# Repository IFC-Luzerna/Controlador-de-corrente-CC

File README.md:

# Controlador de corrente CC

Projeto de um controlador de corrente CC 5A desenvolvido pelos técnicos do IFC - Campus Luzerna para ser utilizado nas disciplinas relacionadas com máquinas e acionamentos elétricos. O objetivo é utilizar esse controlador para acionar um freio acoplado diretamente a um motor de indução trifásico, criando assim um simulador de cargas. Assim, os alunos podem observar as diferentes características de acionamentos quando utilizados em diferentes situações.

Agradecimentos especiais vão para os colaboradores Clecio Jung, Darlan Klotz, Dionathan Luan de Vargas e Marcos Fiorin.

## Descritivo do projeto

Características do controlador de corrente:

- Hardware eletrônico desenvolvido no software Autodesk Eagle versão 9.6.2, e o projeto pode ser adquirido na pasta [circuito eletrônico](./circuito%20eletronico/);

- Firmware do microcontrolador ([Atmega8](https://ww1.microchip.com/downloads/en/DeviceDoc/Atmel-2486-8-bit-AVR-microcontroller-ATmega8_L_datasheet.pdf)) desenvolvido no software Microchip Studio versão 7.0, e os arquivos podem ser adquiridos na pasta [firmware](./firmware/);

- O controlador pode operar como escravo em rede Modbus RS-485:
    - O circuito de comunicação RS-485 é isolado e precisa de alimentação independente (5V ou 24V contínuos);
    - Código utilizado para implementar a comunicação provem da biblioteca [ModBus_RTU_Drivers](https://github.com/RicardoKers/ModBus_RTU_Drivers);
    - Endereço configurável através de chaves dip switch de quatro posições. O valor desejado para o endereço deve ser convertido para binário primeiro, e depois as chaves devem ser configuradas de acordo. Os endereços possíveis estão entre 0 e 15. O endereço 0 não corresponde a um endereço Modbus válido, e portanto, a comunicação Modbus é desabilitada, e o setpoint do controlador passa a ser definido pela entrada analógica 4-20mA (maiores detalhes abaixo).
    - A comunicação dispõe de três registradores de leitura e escrita (funções 3, 6 e 16 do protocolo Modbus):

| Endereço | Range      | Descrição |
| -------- | ---------- | --------- |
| 0        | 200 - 1000 | Valor amostrado da entrada analógica 4-20mA. O valor desse registrador é proporcional à corrente na entrada analógica, sendo que o valor 200 indica corrente de 4mA, e o valor 1000 indica corrente de 20mA. Caso a leitura nesse registrador indique valores inferiores a 200, a entrada está desconectada ou o cabo rompido. Escrever algum valor nesse registrador não terá efeito algum. |
| 1        | 0 - 1000   | Valor amostrado da corrente de carga. O valor desse registrador é proporcional à corrente na carga, sendo que o valor 0 indica 0A, e o valor 1000 indica 5A. Escrever algum valor nesse registrador não terá efeito algum. |
| 2        | 0 - 1000   | Referência (setpoint) de corrente. Segue o mesmo range de unidades do parâmetro anterior. Valor a ser escrito pelo mestre Modbus usado (caso esteja usando comunicação RS-485) |

- O controlador pode ainda receber a referência de corrente (setpoint) a partir da entrada analógica 4-20mA:
    - Para ativar essa opção, deve-se configurar as dip switch de configuração do endereço modbus no valor 0 (todas desabilitadas). Nesse caso, 4mA na entrada representam setpoint de 0A, e 20mA corresponde a referência de 5A. Valores inferiores a 4mA na entrada representam erro (provavelmente o cabo está rompido ou a entrada desconectada), e nesse caso o controlador desliga a carga e o led vermelho liga, indicando um erro;
    - O circuito da entrada analógica é isolado, não necesssita de alimentação independente e o sentido da corrente é arbitrario (funciona do mesmo jeito se a corrente na entrada analógica for positiva ou negativa);

- Quando o led vermelho na placa de circuito eletrônico estiver ligado, um erro ocorreu. Até o momento, apenas um erro é reportado:
    - Quando o setpoint é informado pela entrada analogica e o valor amostrado nessa entrada é inferior a 4mA (provavelmente o cabo está rompido ou a entrada desconectada);

- Na pasta [scada](./scada/) temos uma aplicação desktop simplista desenvolvida no software Elipse E3 (necessário instalá-lo para rodar a aplicação), onde a comunicação com o controlador já está implementada;

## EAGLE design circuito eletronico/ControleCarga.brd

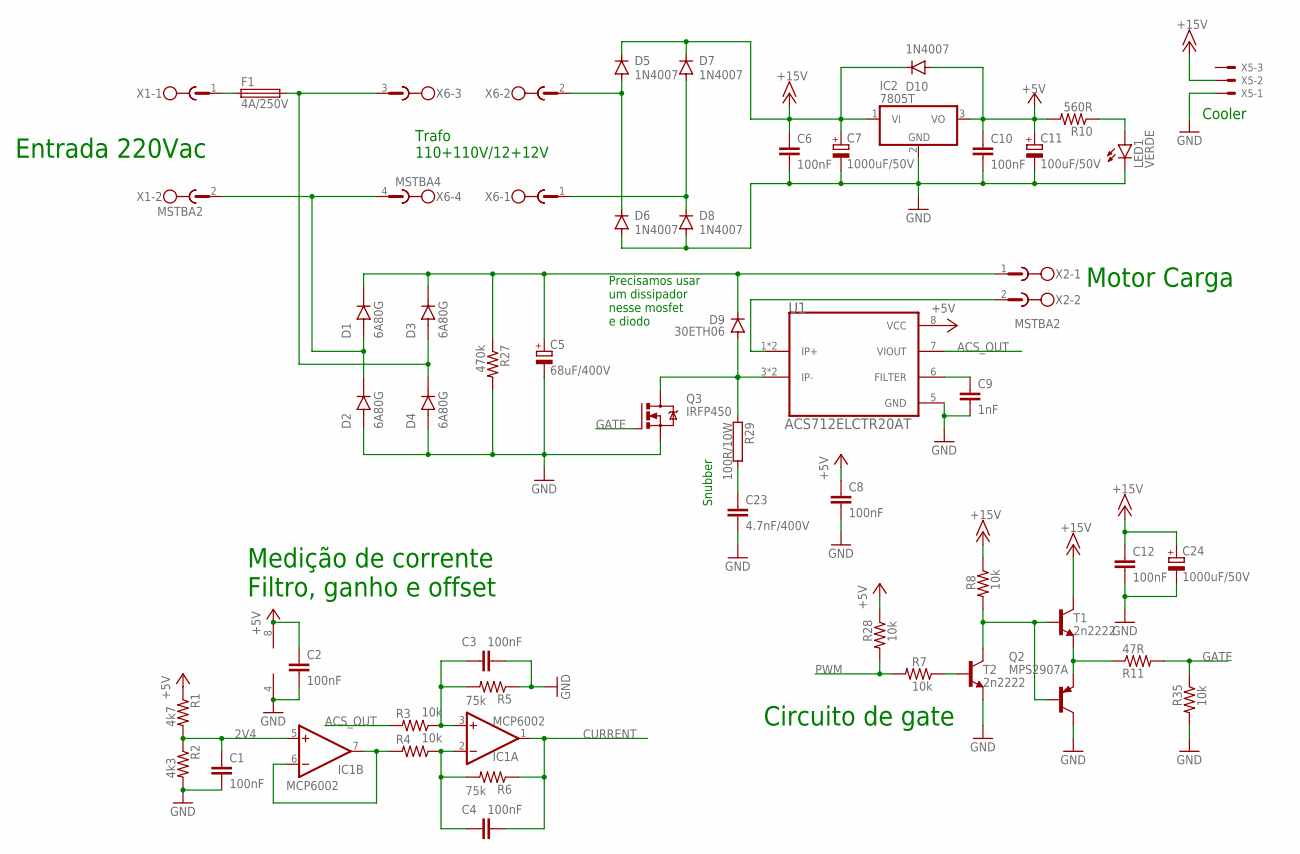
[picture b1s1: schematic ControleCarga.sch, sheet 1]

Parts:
C1, C2, C3, C4, C6, C8, C10, C12: 100nF; C050-025X075
C5: 68uF/400V; E7,5-18
C7, C24: 1000uF/50V; E5-13
C9: 1nF; C025-024X044
C11: 100uF/50V; E3,5-8
C23: 4.7nF/400V; C102-043X133
D1, D2, D3, D4: 6A80G; DIOAD1950W125L885D700
D5, D6, D7, D8, D10: 1N4007; DO41-10
D9: 30ETH06; TO220ACS
F1: 4A/250V; SH22
IC1: MCP6002; SO08
IC2: 7805T; TO220H
LED1: VERDE; LED5MM
Q2: MPS2907A; TO92-CBE
Q3: IRFP450; TO247BV
R1: 4k7; 0207/10
R2: 4k3; 0207/10
R3, R4, R7, R8, R28, R35: 10k; 0207/10
R5, R6: 75k; 0207/10
R10: 560R; 0207/10
R11: 47R; 0207/10
R27: 470k; 0207/10
R29: 100R/10W; KH216-8
T1, T2: 2n2222; TO92-EBC
U1: ACS712ELCTR20AT; SOIC127P600X175-8N
X1, X2: MSTBA2
X5: KK-156-3
X6: MSTBA4

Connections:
2V4: C1.1, IC1.5 (+IN), R1.2, R2.1
+5V: C2.1, C8.1, C10.1, C11.+, D10.A, IC1.8 (V+), IC2.3 (VO), R1.1, R10.2, R28.1, U1.8 (VCC); also elsewhere on the board
+15V: C6.1, C7.+, C12.1, C24.+, D5.C, D7.C, D10.C, IC2.1 (VI), R8.1, T1.C, X5.2
ACS_OUT: R3.2, U1.7 (VIOUT)
CURRENT: C4.2, IC1.1 (OUT), R6.1; also elsewhere on the board
GATE: Q3.G, R11.2, R35.1
GND: C1.2, C2.2, C3.2, C5.-, C6.2, C7.-, C8.2, C9.2, C10.2, C11.-, C12.2, C23.2, C24.-, D2.A, D4.A, D6.A, D8.A, IC1.4 (V-), IC2.2 (GND), LED1.K (C), Q2.C, Q3.S, R2.2, R5.1, R27.2, R35.2, T2.E, U1.5 (GND), X5.1; also elsewhere on the board
unnamed: D7.A, D8.C, X6.1
unnamed: C23.1, R29.2
unnamed: Q2.E, R11.1, T1.E
unnamed: LED1.A, R10.1
unnamed: D3.A, D4.C (K), F1.2, X6.3
unnamed: D1.A, D2.C (K), X1.2, X6.4
unnamed: U1.1 (IP+), U1.2 (IP+), X2.2
unnamed: D9.A, Q3.D, R29.1, U1.3 (IP-), U1.4 (IP-)
unnamed: C5.+, D1.C (K), D3.C (K), D9.C, R27.1, X2.1
unnamed: C9.1, U1.6 (FILTER)
unnamed: IC1.6 (-IN), IC1.7 (OUT), R4.2
unnamed: C4.1, IC1.2 (-IN), R4.1, R6.2
unnamed: C3.1, IC1.3 (+IN), R3.1, R5.2
unnamed: F1.1, X1.1
unnamed: R7.1, T2.B
unnamed: D5.A, D6.C, X6.2
unnamed: Q2.B, R8.2, T1.B, T2.C
PWM: R7.2, R28.2; also elsewhere on the board

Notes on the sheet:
Entrada 220Vac
Medição de corrente Filtro, ganho e offset
Motor Carga
Circuito de gate
Precisamos usar um dissipador nesse mosfet e diodo
Trafo 110+110V/12+12V
Snubber
Cooler

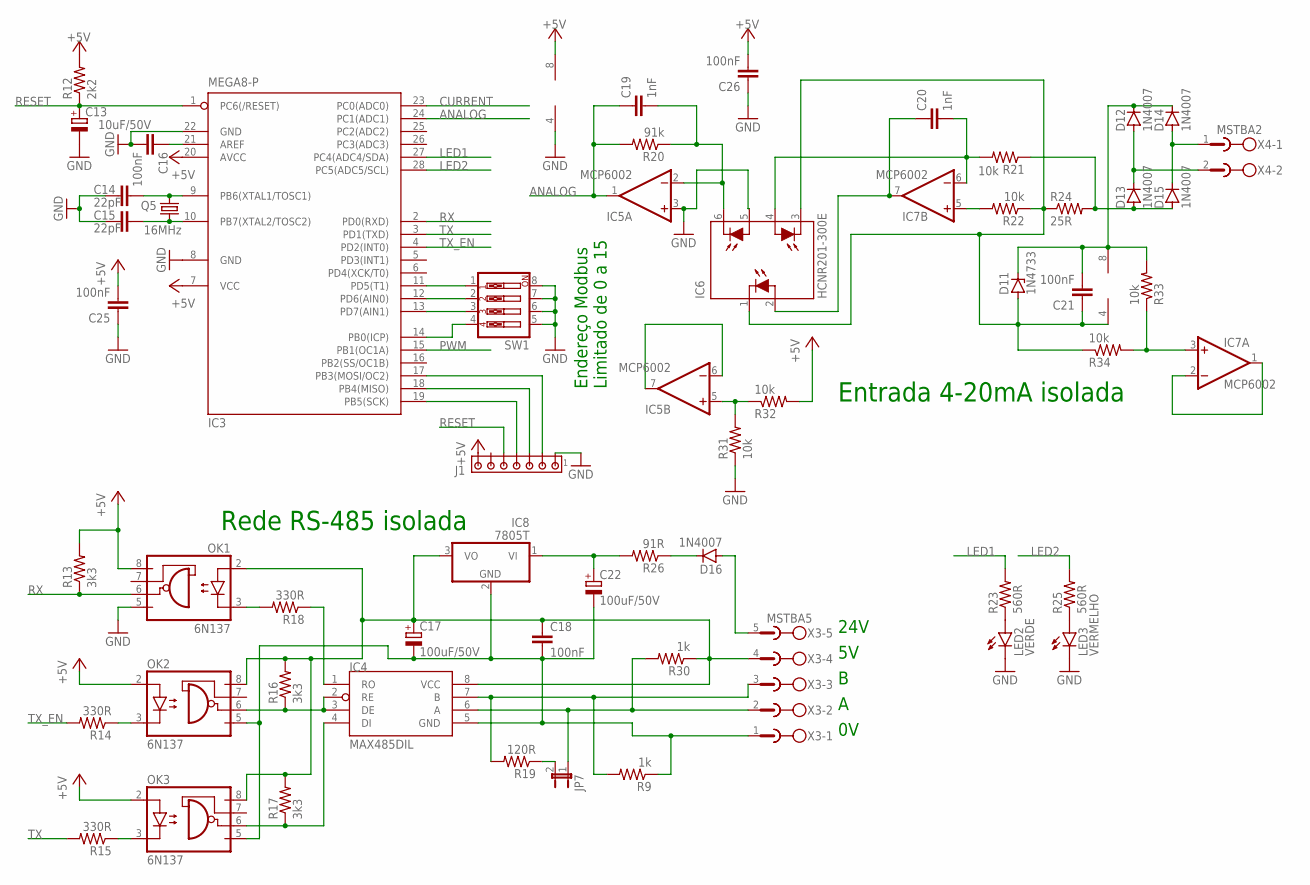
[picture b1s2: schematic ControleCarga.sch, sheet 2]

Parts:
C13: 10uF/50V; E2-5
C14, C15: 22pF; C025-024X044
C16, C18, C21, C25, C26: 100nF; C050-025X075
C17, C22: 100uF/50V; E3,5-8
C19, C20: 1nF; C025-024X044
D11: 1N4733; DO41Z10
D12, D13, D14, D15, D16: 1N4007; DO41-10
IC3: MEGA8-P; DIL28-3
IC4: MAX485DIL; DIL08
IC5, IC7: MCP6002; SO08
IC6: HCNR201-300E; DIP8-400
IC8: 7805T; TO220H
J1: MTA07-100; 10X07MTA
JP7: JP1E; JP1
LED2: VERDE; LED5MM
LED3: VERMELHO; LED5MM
OK1, OK2, OK3: 6N137; DIL08
Q5: 16MHz; HC49/S
R9, R30: 1k; 0207/10
R12: 2k2; 0207/10
R13, R16, R17: 3k3; 0207/10
R14, R15, R18: 330R; 0207/10
R19: 120R; 0207/10
R20: 91k; 0207/10
R21, R22, R31, R32, R33, R34: 10k; 0207/10
R23, R25: 560R; 0207/10
R24: 25R; 0207/10
R26: 91R; 0207/10
SW1: SW_DIP-4; EDG-04
X3: MSTBA5
X4: MSTBA2

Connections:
0V: C17.-, C18.2, C22.-, IC4.5 (GND), IC8.2 (GND), OK2.5 (GND), OK3.5 (GND), R9.1, X3.1
+5V: C25.2, C26.2, IC3.7 (VCC), IC3.20 (AVCC), IC5.8 (V+), J1.7, OK1.8 (VCC), OK2.2 (A), OK3.2 (A), R12.2, R13.2, R32.2; also elsewhere on the board
ANALOG: C19.1, IC3.24 (PC1(ADC1)), IC5.1 (OUT), R20.2
CURRENT: IC3.23 (PC0(ADC0)); also elsewhere on the board
GND: C13.-, C14.2, C15.2, C16.2, C25.1, C26.1, IC3.8 (GND), IC3.22 (GND), IC5.3 (+IN), IC5.4 (V-), IC6.5 (A2), J1.1, LED2.K (C), LED3.K (C), OK1.5 (GND), R31.1, SW1.5, SW1.6, SW1.7, SW1.8; also elsewhere on the board
GNDISO: C21.1, D11.A, IC6.1 (C), IC6.3 (C1), IC7.4 (V-), R22.1, R24.1, R34.1
LED1: IC3.27 (PC4(ADC4/SDA)), R23.2
LED2: IC3.28 (PC5(ADC5/SCL)), R25.2
unnamed: C16.1, IC3.21 (AREF)
unnamed: IC4.2 (RE), IC4.3 (DE), OK2.6 (VO), R16.1
unnamed: D14.A, D15.C, X4.1
unnamed: LED2.A, R23.1
unnamed: IC3.14 (PB0(ICP)), SW1.4
unnamed: IC3.13 (PD7(AIN1)), SW1.3
unnamed: IC3.12 (PD6(AIN0)), SW1.2
unnamed: IC3.11 (PD5(T1)), SW1.1
unnamed: LED3.A, R25.1
unnamed: C21.2, D11.C, D12.C, D14.C, IC7.8 (V+), R33.2
unnamed: IC4.7 (B), R9.2, R19.2, X3.3
unnamed: IC4.6 (A), JP7.1, R30.2, X3.2
unnamed: IC4.4 (DI), OK3.6 (VO), R17.1
unnamed: OK1.3 (C), R18.2
unnamed: IC4.1 (RO), R18.1
unnamed: OK2.3 (C), R14.1
unnamed: OK3.3 (C), R15.1
unnamed: IC3.19 (PB5(SCK)), J1.4
unnamed: JP7.2, R19.1
unnamed: C19.2, IC5.2 (-IN), IC6.6 (C2), R20.1
unnamed: C22.+, IC8.1 (VI), R26.2
unnamed: IC5.6 (-IN), IC5.7 (OUT)
unnamed: IC7.1 (OUT), IC7.2 (-IN)
unnamed: C20.1, IC6.2 (A), IC7.7 (OUT)
unnamed: IC7.5 (+IN), R22.2
unnamed: D13.A, D15.A, R21.1, R24.2
unnamed: C20.2, IC6.4 (A1), IC7.6 (-IN), R21.2
unnamed: IC3.18 (PB4(MISO)), J1.3
unnamed: C17.+, C18.1, IC4.8 (VCC), IC8.3 (VO), OK1.2 (A), OK2.8 (VCC), OK3.8 (VCC), R16.2, R17.2, R30.1, X3.4
unnamed: IC3.17 (PB3(MOSI/OC2)), J1.2
unnamed: D16.A, X3.5
unnamed: D12.A, D13.C, X4.2
unnamed: C14.1, IC3.9 (PB6(XTAL1/TOSC1)), Q5.2
unnamed: C15.1, IC3.10 (PB7(XTAL2/TOSC2)), Q5.1
unnamed: D16.C, R26.1
unnamed: IC5.5 (+IN), R31.2, R32.1
unnamed: IC7.3 (+IN), R33.1, R34.2
PWM: IC3.15 (PB1(OC1A)); also elsewhere on the board
RESET: C13.+, IC3.1 (PC6(/RESET)), J1.5, R12.1
RX: IC3.2 (PD0(RXD)), OK1.6 (VO), R13.1
TX: IC3.3 (PD1(TXD)), R15.2
TX_EN: IC3.4 (PD2(INT0)), R14.2

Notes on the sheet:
Rede RS-485 isolada
Entrada 4-20mA isolada
Endereço Modbus Limitado de 0 a 15
24V

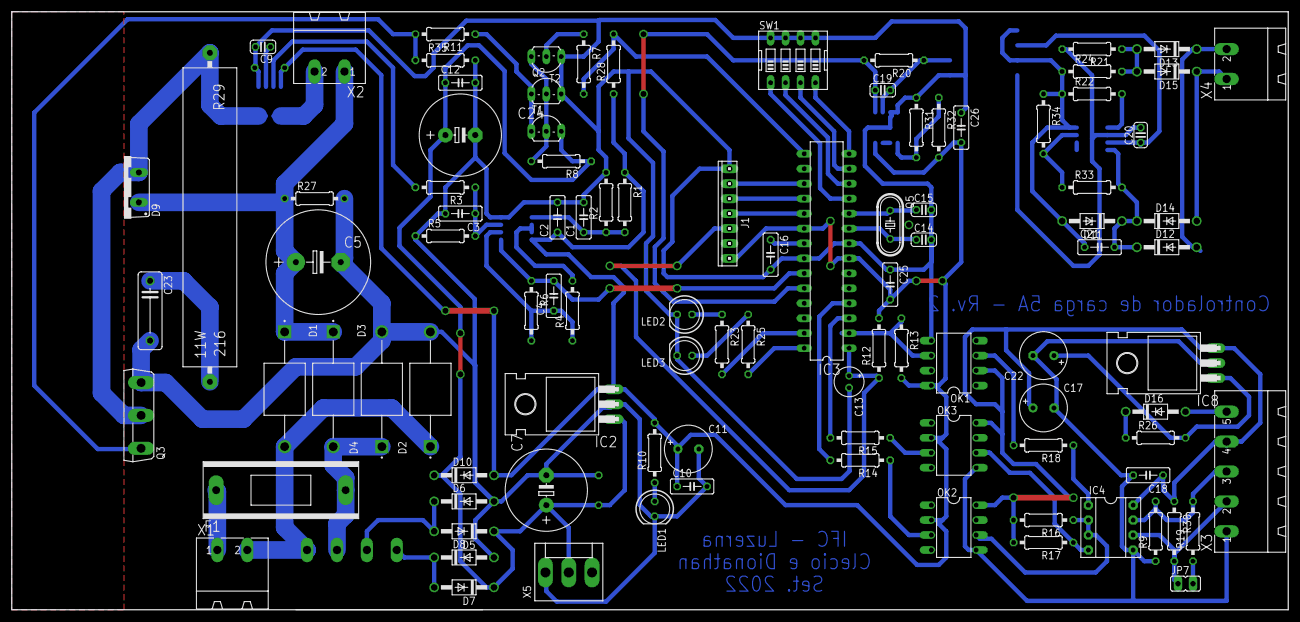
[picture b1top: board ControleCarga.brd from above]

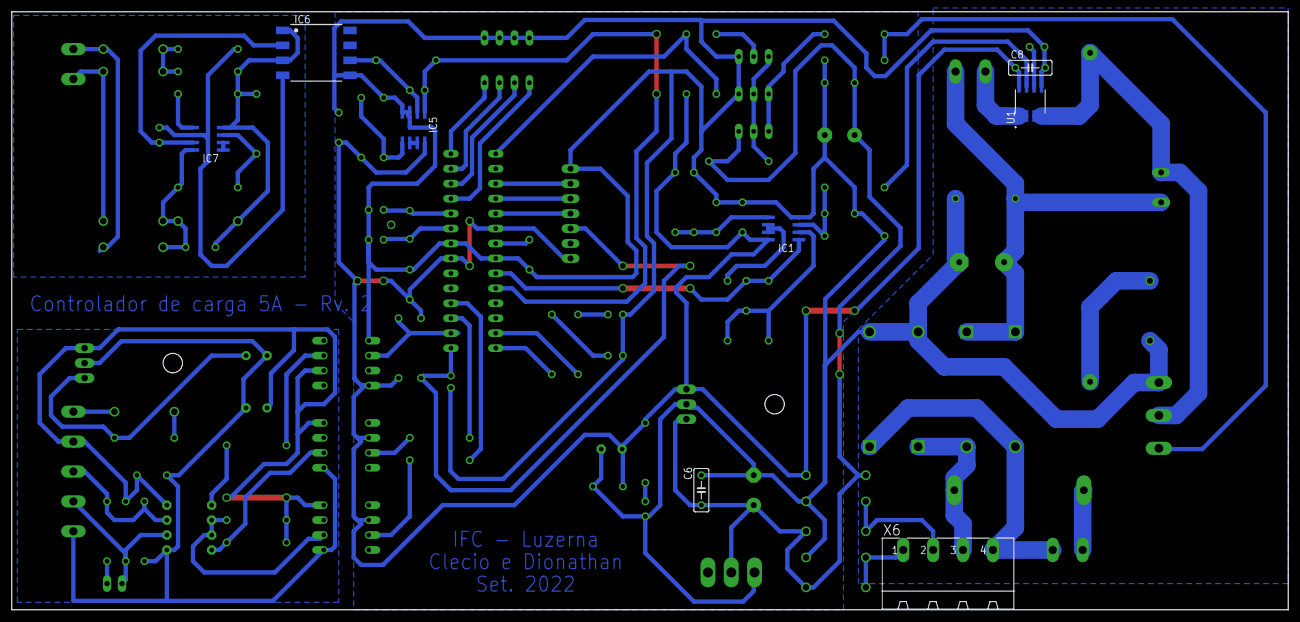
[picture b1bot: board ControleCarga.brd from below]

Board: 2 copper layers, 216.8 x 101.6 mm, 107 parts (8 on the bottom side), 71 nets.

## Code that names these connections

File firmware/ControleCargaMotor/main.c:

//-------------------------------------------------------------------------------------------------------
#define F_CPU 16000000UL

#include <avr/io.h>
#include <avr/interrupt.h>
#include <util/delay.h>
#include "ModBusSlave.h"

//-------------------------------------------------------------------------------------------------------
// Constants

// LED test
#define SET_GREEN_LED()		(PORTC  |= (1<<PC4))
#define CLEAR_GREEN_LED()	(PORTC  &= ~(1<<PC4))
#define TOOGLE_GREEN_LED()	(PORTC  ^= (1<<PC4))
#define SET_RED_LED()		(PORTC  |= (1<<PC5))
#define CLEAR_RED_LED()		(PORTC  &= ~(1<<PC5))
#define TOOGLE_RED_LED()	(PORTC  ^= (1<<PC5))

// Dip Switch
#define DIP_SWITCH()		((uint16_t)((((~PIND) & 0xF0)) >> 4))

// ajustes das entradas analógicas
#define ANALOG_INPUT_GAIN	((uint32_t)1074)
#define ANALOG_INPUT_OFFSET ((uint32_t)3769)
#define CURRENT_GAIN		((int32_t)1311)
#define CURRENT_OFFSET		((int32_t)-45462)

// Máximos valores para o PWM e setpoint
#define PWM_MAX					800
#define PWM_LIMIT				180
#define SETPOINT_MAX			1000

// Parametros da entrada analógica
#define ANALOG_INPUT_TOO_LOW	150
#define ANALOG_INPUT_MIN		200
#define ANALOG_INPUT_MAX		1000

// Modo de controle de corrente (open or closed loop)
#define CLOSED_LOOP				1

// Controller adjust
#define GAIN_K1					200
#define GAIN_K2					190

//-------------------------------------------------------------------------------------------------------
// Global variables

/*	entrada analógica isolada 4-20mA
	range: 200-1000
	se o valor for < 200, a corrente é inferior a 4mA
	e provavelmente o cabo está rompido
*/
volatile uint16_t analog_input = 0;
/*	medição de corrente na carga 0-5A
	range: 0-1000
*/
volatile uint16_t current = 0;
/*	setpoint para controle de corrente
	range: 0-1000
*/
volatile uint16_t setpoint = 0;

//-------------------------------------------------------------------------------------------------------
// Run PI control

struct PI {
	int16_t previousError;
	int32_t controlSignal;
};

void piClear(struct PI *pi) {
	pi->previousError = 0;
	pi->controlSignal = 0;
}

struct PI piCurrent;

uint16_t piControl(struct PI *pi, uint16_t setPoint, uint16_t feedBack)
{
	int16_t error = setPoint - feedBack;
	pi->controlSignal += GAIN_K1 * error - GAIN_K2 * pi->previousError;
	pi->previousError = error;
	
	if (pi->controlSignal >= (int32_t)PWM_LIMIT*1000) {
		pi->controlSignal = (int32_t)PWM_LIMIT*1000;
	} else if (pi->controlSignal < 0) {
		pi->controlSignal = 0;
	}

	return (uint16_t)(pi->controlSignal/1000);
}

static inline void controle(void) {
	// operando com setpoint enviado pela entrada analógica
	if (ModBus.end_modbus == 0) {
		if (analog_input < ANALOG_INPUT_MIN) {
			setpoint  = 0;
		} else if (analog_input > ANALOG_INPUT_MAX) {
			setpoint = SETPOINT_MAX;
		} else {
			uint32_t sp32 = ((uint32_t)SETPOINT_MAX)*((uint32_t)(analog_input - ANALOG_INPUT_MIN));
			setpoint = (uint16_t) (sp32/((uint32_t)(ANALOG_INPUT_MAX - ANALOG_INPUT_MIN)));
		}
	}
	
	#if CLOSED_LOOP
		OCR1A = piControl(&piCurrent, setpoint, current);
	#else // open loop
		OCR1A = setpoint;
	#endif
}

static inline uint16_t dip_switch(void) {
	const uint16_t bit0 = (PIND&(1<<PD5)) ? 0:1;
	const uint16_t bit1 = (PIND&(1<<PD6)) ? 0:1;
	const uint16_t bit2 = (PIND&(1<<PD7)) ? 0:1;
	const uint16_t bit3 = (PINB&(1<<PB0)) ? 0:1;
	return ((bit3<<3)|(bit2<<2)|(bit1<<1)|(bit0<<0));
}

//-------------------------------------------------------------------------------------------------------
// ADC - Entradas Analógicas

// O ADC do Atmega8 não é muito bom. Segundo o datasheet, não deveriamos usar uma frequencia maior do que 200kHz,
// o que restringe bastante a frequência de operação. Além disso, o ADC consome 13 ciclos para fazer a medição,
// o que implica na frequência de amostragem máxima de 200/13 = 15,38kHz (medindo apenas um canal).
// E acima de tudo isso, não existe um meio para medir continuamente varios canais, temos de tratar isso no 
// codigo da interupção, o que torna a frequencia de amostragem variavel com o codigo gravado no processador.
ISR(ADC_vect)
{
	cli();
	// fs = 4.54kHz, T = 220us (medido experimentalmente com o osciloscópio)
	uint32_t adc = ADCW;
	
	// Le próximo canal
	ADMUX ^= (1<<MUX0);
	ADCSRA |= (1<<ADSC);
	
	if (ADMUX & (1<<MUX0)) {
		const int32_t current32 = (CURRENT_GAIN * (int32_t)adc + CURRENT_OFFSET)/1000;
		current = current32 > 0 ? (uint16_t)(current32) : 0;
		controle();
	} else {
		analog_input = (uint16_t)((ANALOG_INPUT_GAIN * (uint32_t)adc + ANALOG_INPUT_OFFSET)/1000);
	}
	sei();
}

//-------------------------------------------------------------------------------------------------------
int main(void)
{
	// Leds
	DDRC |= (1<<DDC4) | (1<<DDC5);
	// Dip Switch - Liga os resistores de pull-up
	PORTD |= (1<<PD7)|(1<<PD6)|(1<<PD5);
	PORTB |= (1<<PB0);
	
	//-----------------------------------
	// ADC - Entradas Analógicas
	// Frequencia de Amostragem = 4.8kHz (medição de dois canais em sequência)
	ADMUX = (1<<REFS0);
	// Prescaler = /128, conversion cycles = 13, f = 9.6kHz, T = 200us
	ADCSRA = (1<<ADEN)|(1<<ADIE)|(1<<ADPS2)|(1<<ADPS1)|(1<<ADPS0);
	// Inicia nova conversão
	ADCSRA |= (1<<ADSC);

	//-----------------------------------
	// Timer 1 - PWM
	PORTB |= (1<<PB1);
	TCNT1 = 0;
	OCR1A = 0;
	ICR1 = PWM_MAX; // Freq = 10kHz
	TCCR1A = (1 << COM1A1)|(1 << COM1A0)|(1 << WGM11); // Set OC1A on Compare Match and clear at BOTTOM
	TCCR1B = (1 << WGM13)|(1 << WGM12)|(1 << CS10); // Mode 14, Fast PWM, overflow on ICR1, set prescaler to 1
	DDRB |= (1<<DDB1);
	
	usart_init(); // inicia a comunicação serial utilizada na ModBus
	ModBusReset(); // prepara para receber a transmissão
	
	// Inicializa variaveis internas do controlador
	piClear(&piCurrent);
	
	// Enable interrupts
	sei();
	
	uint32_t counter = 0;
	
	// Main loop
	while (1)
	{
		counter++;
		if (counter >= 50000) {
			counter = 0;
			TOOGLE_GREEN_LED();
		}
		
		if (ModBus.status == aguardando || ModBus.end_modbus == 0) {
			uint8_t novo_endereco = dip_switch();
			if (ModBus.end_modbus != novo_endereco) {
				setpoint = 0; // reseta o setpoint para desligar o sistema
				piClear(&piCurrent);
				ModBus.data_reg[2] = 0;
				ModBus.end_modbus = novo_endereco;
			}
		}
		
		if (ModBus.end_modbus != 0)	{
			if (ModBus.status == processando) {
				ModBusProcess(); // inicia o processamento do pacote
			}
			ModBus.data_reg[0] = analog_input;
			ModBus.data_reg[1] = current;
			if (ModBus.data_reg[2] < SETPOINT_MAX) {
				setpoint = ModBus.data_reg[2];
			} else {
				setpoint = SETPOINT_MAX;
			}
		}
		
		if ((ModBus.end_modbus == 0) && (analog_input < ANALOG_INPUT_TOO_LOW)) {
			// liga led vermelho para indicar que a entrada analógica está recebendo menos de 4mA
			SET_RED_LED();
		} else {
			CLEAR_RED_LED();
		}
	}
}
//-------------------------------------------------------------------------------------------------------

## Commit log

2022-09-05 Commit inicial
